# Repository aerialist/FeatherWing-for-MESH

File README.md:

# FeatherWing-for-MESH

A board to connect Adafruit Feather line of microcontroller boards to Sony MESH GPIO tag.

* https://www.adafruit.com/feather
* http://meshprj.com/en/

It also acts as a GPIO accessory for Sony MESH GPIO tag, featuring three buttons for Digital In, three LED's for Digital Out, a potentiometer for Analog In and another LED for PWM Out.

See [Wiki](https://github.com/aerialist/FeatherWing-for-MESH/wiki) for documentation.

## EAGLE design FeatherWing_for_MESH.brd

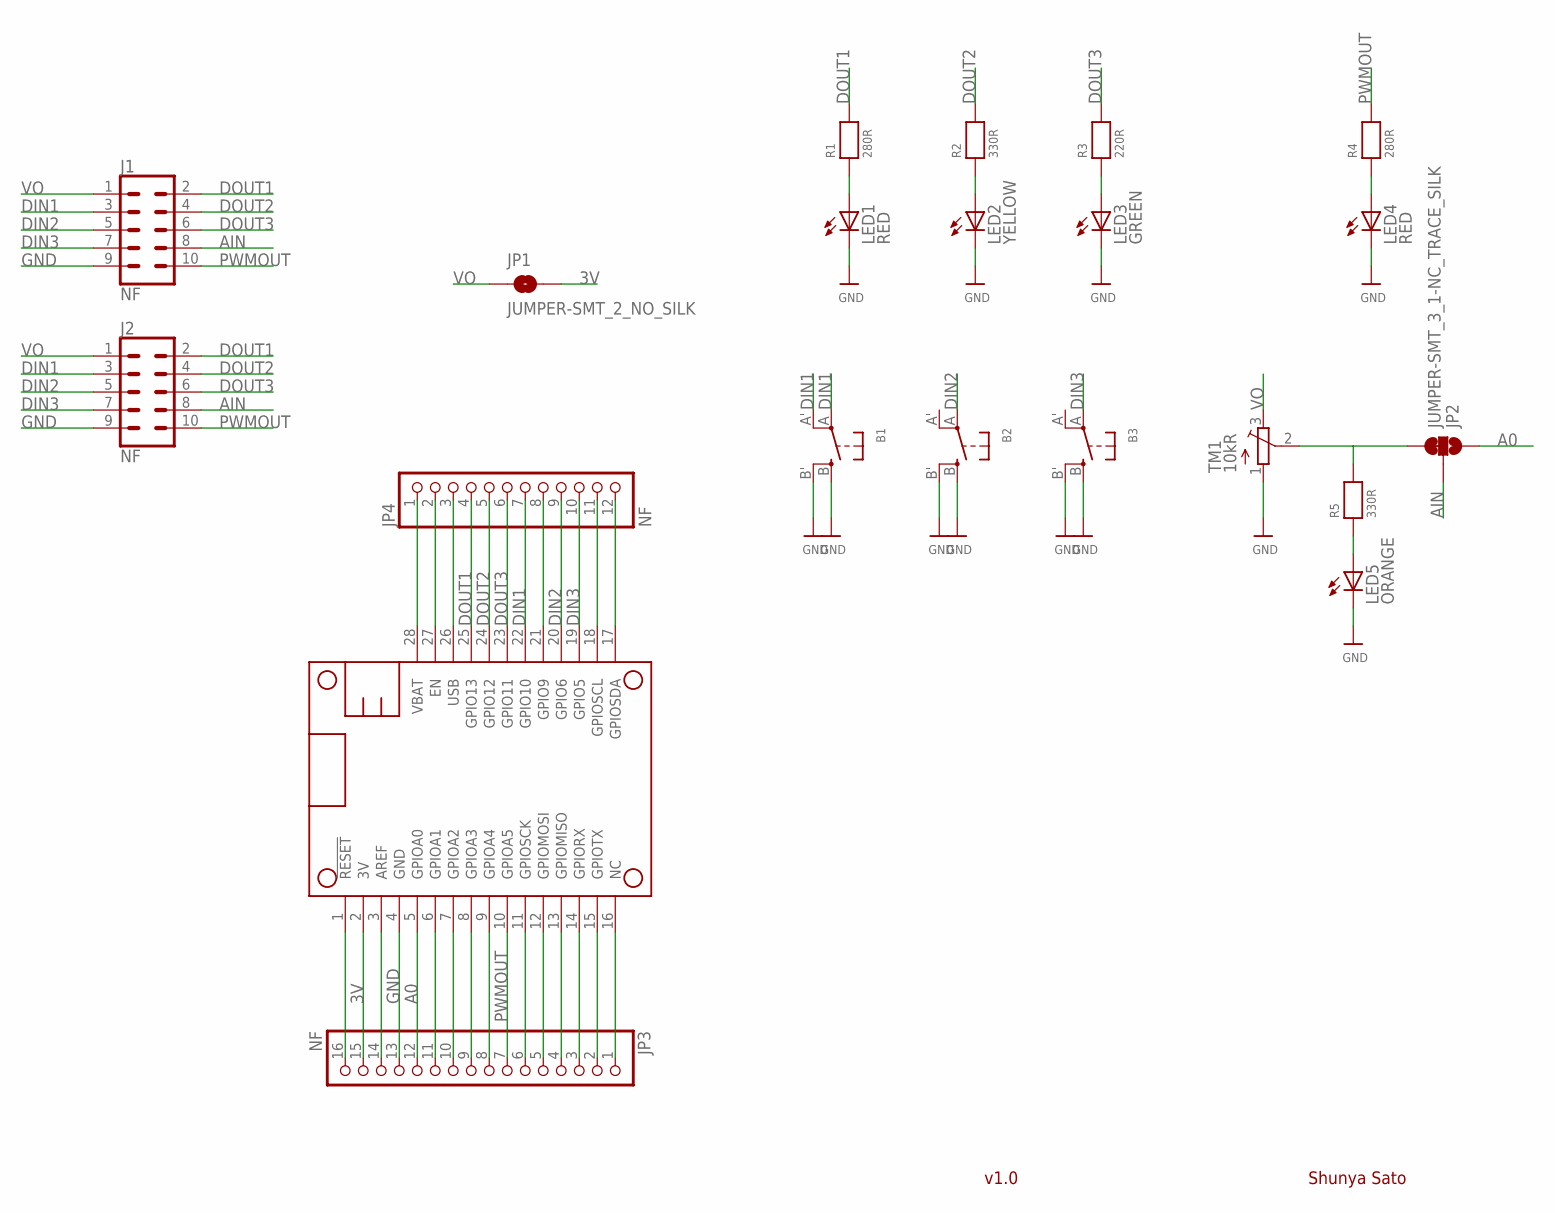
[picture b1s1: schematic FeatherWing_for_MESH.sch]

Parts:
B1, B2, B3: SWITCH_TACT_SMT4.6X2.8; BTN_KMR2_4.6X2.8
J1, J2: NF; 2X5_NOSILK
JP1: JUMPER-SMT_2_NO_SILK; SMT-JUMPER_2_NO_SILK
JP2: JUMPER-SMT_3_1-NC_TRACE_SILK; SMT-JUMPER_3_1-NC_TRACE_SILK
JP3: NF; 1X16_ROUND_76MIL
JP4: NF; 1X12_ROUND_76MIL
LED1, LED4: RED; CHIPLED_0805
LED2: YELLOW; CHIPLED_0805
LED3: GREEN; CHIPLED_0805
LED5: ORANGE; CHIPLED_0805
MS1: FEATHERWING
R1, R4: 280R; 0805_NOTHERMALS
R2, R5: 330R; 0805_NOTHERMALS
R3: 220R; 0805_NOTHERMALS
TM1: 10kR; TC33X

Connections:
3V: JP1.2, JP3.15, MS1.2 (3V)
A0: JP2.1, JP3.12, MS1.5 (GPIOA0)
AIN: J1.8, J2.8, JP2.2
AREF: JP3.14, MS1.3 (AREF)
DIN1: B1.A, B1.A' (P1), J1.3, J2.3, JP4.7, MS1.22 (GPIO10)
DIN2: B2.A, J1.5, J2.5, JP4.9, MS1.20 (GPIO6)
DIN3: B3.A, J1.7, J2.7, JP4.10, MS1.19 (GPIO5)
DOUT1: J1.2, J2.2, JP4.4, MS1.25 (GPIO13), R1.2
DOUT2: J1.4, J2.4, JP4.5, MS1.24 (GPIO12), R2.2
DOUT3: J1.6, J2.6, JP4.6, MS1.23 (GPIO11), R3.2
GND: B1.B (S), B1.B' (S1), B2.B (S), B2.B' (S1), B3.B (S), B3.B' (S1), J1.9, J2.9, JP3.13, LED1.C, LED2.C, LED3.C, LED4.C, LED5.C, MS1.4 (GND), TM1.1 (A)
unnamed: JP4.2, MS1.27 (EN)
unnamed: JP3.1, MS1.16 (NC)
unnamed: JP3.2, MS1.15 (GPIOTX)
unnamed: JP3.3, MS1.14 (GPIORX)
unnamed: JP3.4, MS1.13 (GPIOMISO)
unnamed: JP3.5, MS1.12 (GPIOMOSI)
unnamed: JP3.6, MS1.11 (GPIOSCK)
unnamed: JP3.8, MS1.9 (GPIOA4)
unnamed: JP3.9, MS1.8 (GPIOA3)
unnamed: JP3.10, MS1.7 (GPIOA2)
unnamed: JP3.11, MS1.6 (GPIOA1)
unnamed: LED1.A, R1.1
unnamed: LED2.A, R2.1
unnamed: JP3.16, MS1.1 (!RESET)
unnamed: JP4.8, MS1.21 (GPIO9)
unnamed: JP4.11, MS1.18 (GPIOSCL)
unnamed: JP4.12, MS1.17 (GPIOSDA)
unnamed: LED3.A, R3.1
unnamed: LED4.A, R4.1
unnamed: JP2.3, R5.2, TM1.2 (S)
unnamed: LED5.A, R5.1
PWMOUT: J1.10, J2.10, JP3.7, MS1.10 (GPIOA5), R4.2
USB: JP4.3, MS1.26 (USB)
VBAT: JP4.1, MS1.28 (VBAT)
VO: J1.1, J2.1, JP1.1, TM1.3 (E)

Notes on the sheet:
Shunya Sato
v1.0

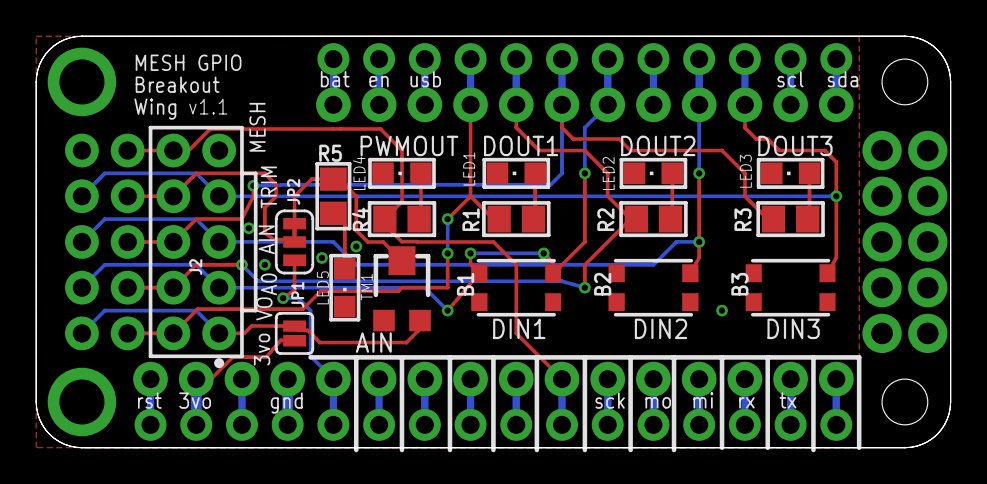
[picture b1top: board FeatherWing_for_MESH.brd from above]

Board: 2 copper layers, 50.8 x 22.9 mm, 21 parts (1 on the bottom side), 36 nets.

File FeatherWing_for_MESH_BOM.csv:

"Part";"Value";"Device";"Package";"Description";"";
"B1";"";"SWITCH_TACT_SMT4.6X2.8";"BTN_KMR2_4.6X2.8";"SMT Tact Switches";"";
"B2";"";"SWITCH_TACT_SMT4.6X2.8";"BTN_KMR2_4.6X2.8";"SMT Tact Switches";"";
"B3";"";"SWITCH_TACT_SMT4.6X2.8";"BTN_KMR2_4.6X2.8";"SMT Tact Switches";"";
"J1";"NF";"CONN_05X2NO_SILK";"2X5_NOSILK";"Multi connection point. Often used as Generic Header-pin footprint for 0.1 inch spaced/style header connections";"";
"J2";"NF";"CONN_05X2NO_SILK";"2X5_NOSILK";"Multi connection point. Often used as Generic Header-pin footprint for 0.1 inch spaced/style header connections";"";
"JP1";"JUMPER-SMT_2_NC_TRACE_SILK";"JUMPER-SMT_2_NC_TRACE_SILK";"SMT-JUMPER_2_NC_TRACE_SILK";"Normally closed trace jumper";"";
"JP2";"JUMPER-SMT_3_1-NC_TRACE_SILK";"JUMPER-SMT_3_1-NC_TRACE_SILK";"SMT-JUMPER_3_1-NC_TRACE_SILK";"Normally closed trace jumper (1 of 2 connections)";"";
"JP3";"NF";"HEADER-1X16_76MIL";"1X16_ROUND_76MIL";"PIN HEADER";"";
"JP4";"NF";"HEADER-1X1276MIL";"1X12_ROUND_76MIL";"";"";
"LED1";"RED";"LEDCHIPLED_0805";"CHIPLED_0805";"LED";"";
"LED2";"YELLOW";"LEDCHIPLED_0805";"CHIPLED_0805";"LED";"";
"LED3";"GREEN";"LEDCHIPLED_0805";"CHIPLED_0805";"LED";"";
"LED4";"RED";"LEDCHIPLED_0805";"CHIPLED_0805";"LED";"";
"LED5";"ORANGE";"LEDCHIPLED_0805";"CHIPLED_0805";"LED";"";
"MS1";"FEATHERWING";"FEATHERWING";"FEATHERWING";"";"";
"R1";"280R";"RESISTOR0805_NOTHERMALS";"0805_NOTHERMALS";"Resistors";"";
"R2";"330R";"RESISTOR0805_NOTHERMALS";"0805_NOTHERMALS";"Resistors";"";
"R3";"220R";"RESISTOR0805_NOTHERMALS";"0805_NOTHERMALS";"Resistors";"";
"R4";"280R";"RESISTOR0805_NOTHERMALS";"0805_NOTHERMALS";"Resistors";"";
"R5";"330R";"RESISTOR0805_NOTHERMALS";"0805_NOTHERMALS";"Resistors";"";
"TM1";"10kR";"TRIMPOTTC33X";"TC33X";"SMT trimmer potentiometer part number TC33X";"";

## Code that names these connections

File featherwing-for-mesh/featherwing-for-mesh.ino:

// Pin connections
// MESH <-> Feather
#define AIN A0
#define PWMOUT A5
#define DOUT1 13
#define DOUT2 12
#define DOUT3 11
#define DIN1 10
#define DIN2 6
#define DIN3 5

int dins[] = {DIN1, DIN2, DIN3};
int douts[] = {DOUT1, DOUT2, DOUT3};

void setup() {
  Serial.begin(115200);
  Serial.println("Feather Wing for Sony MESH");
  
  // set pin mode of Feather
  // Note that pin naming is from MESH's point of view
  // i.e. DIN is Digital Input for MESH which is OUTPUT for Feather
  pinMode(AIN, OUTPUT);
  pinMode(PWMOUT, INPUT);
  pinMode(DOUT1, INPUT);
  pinMode(DOUT2, INPUT);
  pinMode(DOUT3, INPUT);
  pinMode(DIN1, OUTPUT);
  pinMode(DIN2, OUTPUT);
  pinMode(DIN3, OUTPUT);
  
  digitalWrite(DIN1, HIGH);
  digitalWrite(DIN2, HIGH);
  digitalWrite(DIN3, HIGH);

  //test_din();
}

void loop() {
  // uncomment each lines to test
  // test_din();
  // test_dout();  
  // test_pwmout();
  // test_ain();
}

void test_ain(void){
  for(int i=0; i<255; i++){
    analogWrite(AIN, i);
    Serial.println(i);
    delay(30);
  }
  for(int i=255; i<0; i--){
    analogWrite(AIN, i);
    Serial.println(i);
    delay(30);
  }
}

void test_pwmout(void){
  digitalWrite(DIN1, LOW);
  for (int i=0; i<10; i++){
    unsigned long duration = pulseIn(PWMOUT, HIGH);
    Serial.println(duration);
    delay(1000);  
  }
  digitalWrite(DIN1, HIGH);
  delay(5000);
}

void test_dout(void){
  for(int i=0; i<3; i++){
    digitalWrite(dins[i], LOW);
    delay(3000);
    print_dout();
    delay(1000);
    digitalWrite(dins[i], HIGH);
    delay(3000);
    print_dout();
  }
}

void print_dout(void){
  Serial.println("DOUT status");
  for (int i=0; i<3; i++){
    int btn = digitalRead(douts[i]);
    Serial.print(i);
    Serial.print(": ");
    Serial.println(btn);    
  }
}

void test_din(void){
  int delaytime = 3000;

  Serial.println("Going to test DIN");
  for (int i=0; i<3; i++){
    digitalWrite(dins[i], LOW);
    Serial.print(i);
    Serial.println(": LOW");
    delay(delaytime);
    digitalWrite(dins[i], HIGH);
    Serial.print(i);
    Serial.println(": HIGH");
    delay(delaytime);
  }
}

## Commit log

2018-02-15 Initial commit. v1.0
2018-03-29 Add license
2018-05-02 Add Arduino example
2018-05-03 v1.1 Add Mesh pin1 marking, move LEDs away from buttons, default not to connect 3V and Vout. Panelized garber.
2018-05-03 Add BOM and gitignore

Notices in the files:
parts and their libraries:
SparkFun-Connectors: Licensing: Creative Commons ShareAlike 4.0 International - https://creativecommons.org/licenses/by-sa/4.0
